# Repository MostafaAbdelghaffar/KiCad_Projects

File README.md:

# KiCad_Projects
Beginner friendly projects, to practice KiCad and design PCBs using KiCad

### Introduction: 
This Repo is made for beginner friendly KiCad design for training purposes. This acts as a portfolio for the trainings and projets I have worked for designing PCBs.

The first one "StopLight" is meant to be familiar with the KiCad tool as the training that I had was on Altium. It is a simple pcb design with 3 LEDs and 3 Resistors and a connector.

As a PCB designer you need to know the following:
1. Know the capabilities of your PCB manufacturer
2. Have a solid understanding of the PCB design process
3. Have a solid understanding of the PCB Design tools
4. Have the patience to build up your skills

### Description: 
#### The following are the GENERAL steps for designing PCB in order

1. Define design rules and requirement
2. Create a schematic: Detailed schematic of the board's electrical design
3. Place components (taking into account signal integrity, thermal management and manufacturability)
4. Route traces: use color coded route tracing to create cirtual pathways between components and determine ther most efficient design layout.
5. Add labels and identifiers: including markers and reference designator or other identifying information to the layout.
6. Insert drill holes

#### The following are the KiCad design workflow in order:
<div align="center">
  
  <p><em>Figure 1: KiCad Design Workflow<sup><a href="#footnote-1">1</a></sup></em></p>
</div>

### PCB design process:

<div align="center">
  
  <p><em>Figure 2: PCB Design Process<sup><a href="#footnote-2">2</b></sup></em></p>
</div>

### Results

<div align="center">
  
  <p><em>Figure 3: Schematic Capture</em></p>
</div>

<div align="center">
  
  <p><em>Figure 4: PCB Design</em></p>
</div>

<div align="center">
  
  <p><em>Figure 5: PCB 3D View</em></p>
</div>

### References:
* **Footnote 1**: Image source: [Tech Explorations](https://techexplorations.com/wp-content/uploads/2019/05/S1_KicadDesignProcess-1024x619.jpg)
* <b id="footnote-2"></a>**Footnote 2**: Image source: [TronicsZone](https://www.tronicszone.com/tronicszone/wp-content/uploads/2020/02/PCB-Manufacturing-Steps.png)

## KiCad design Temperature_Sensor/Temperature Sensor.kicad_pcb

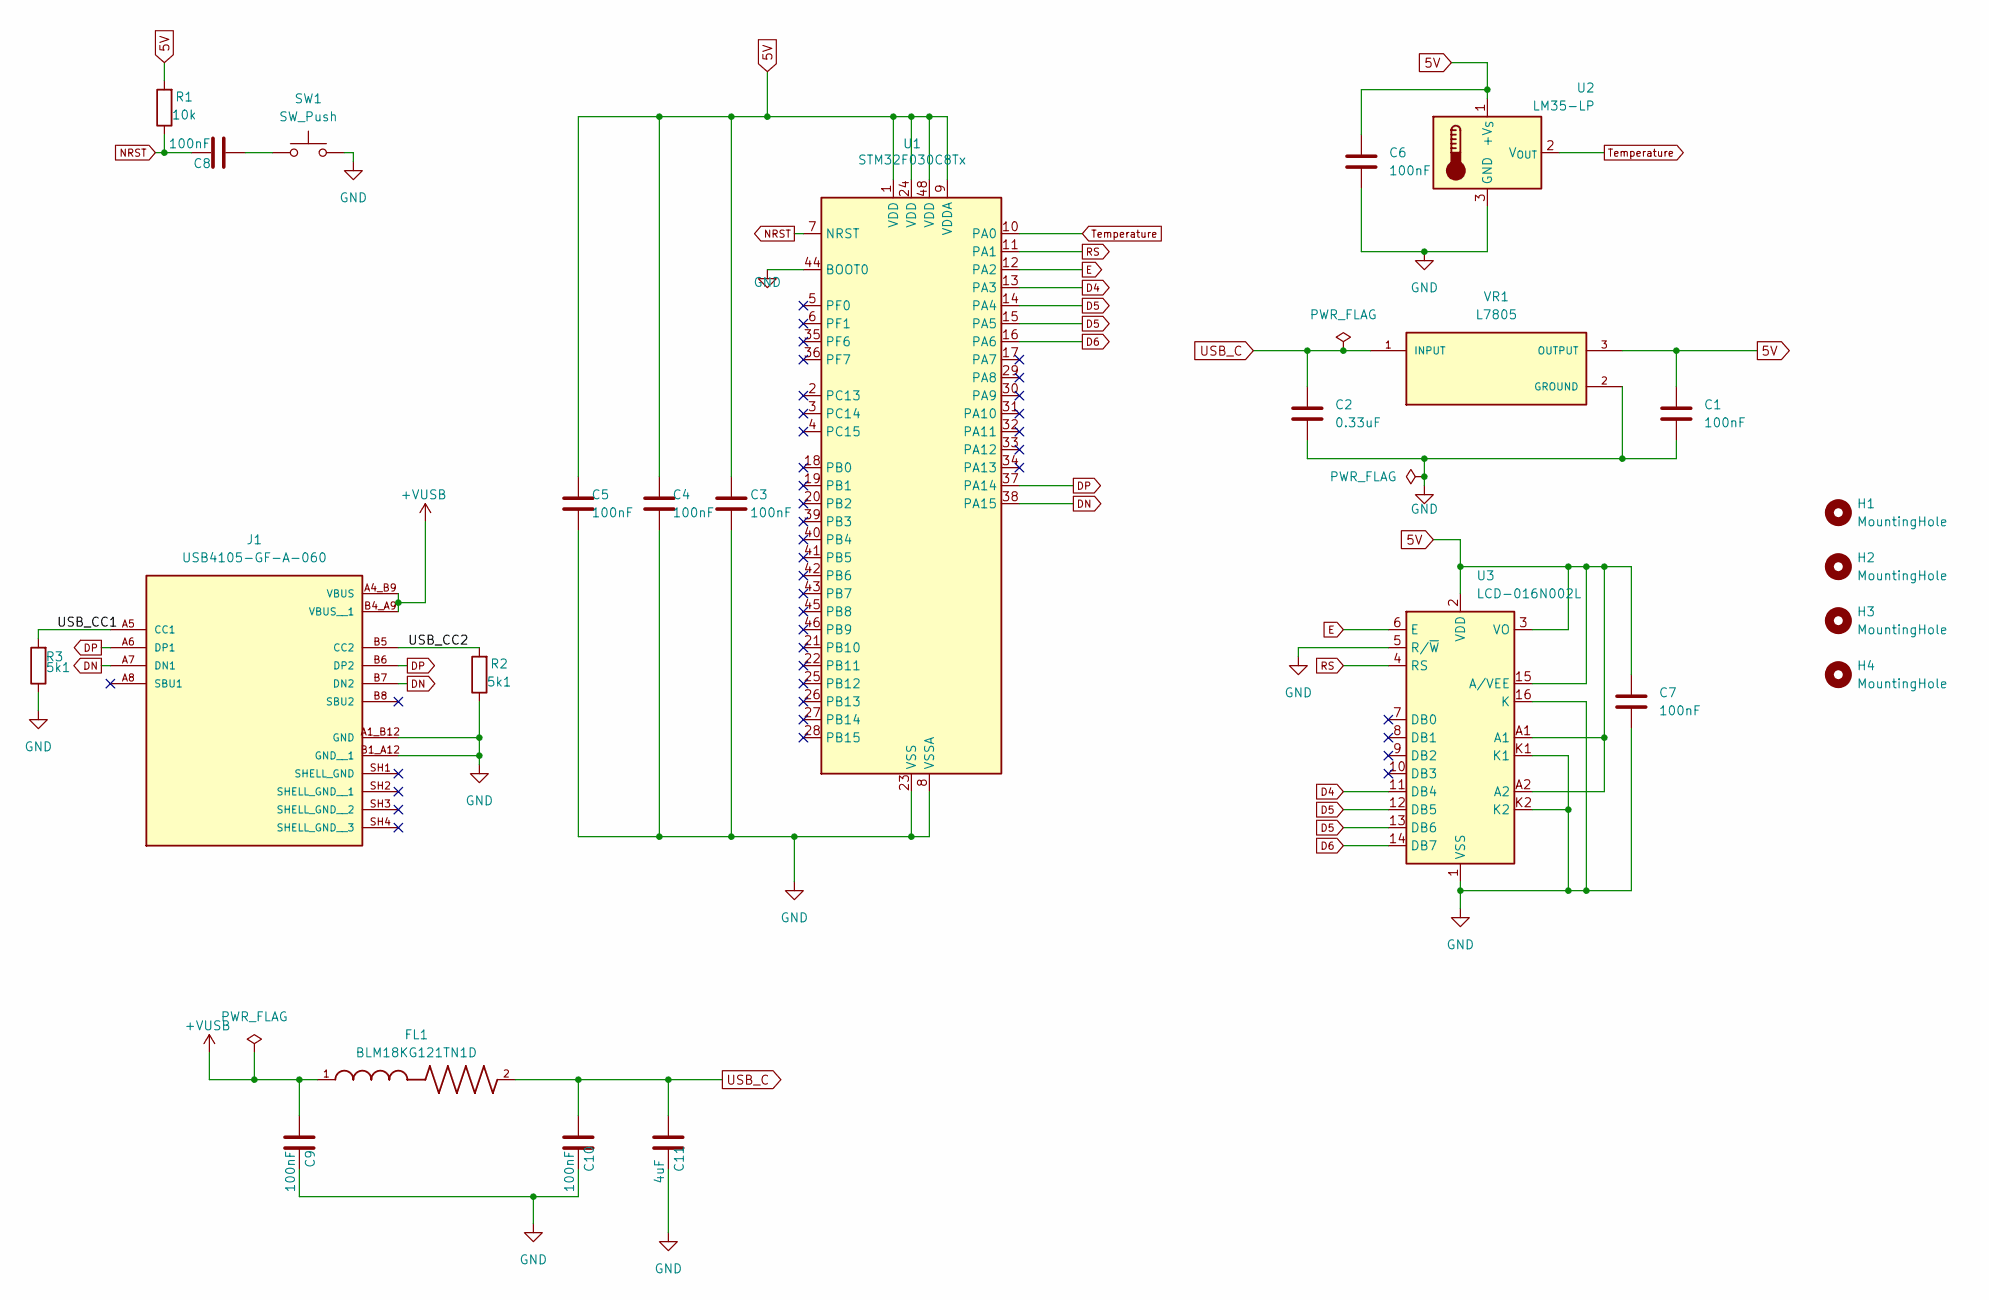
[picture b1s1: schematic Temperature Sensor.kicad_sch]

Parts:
C1, C3, C4, C5, C6, C7, C8, C9, C10: 100nF; C_0603_1608Metric
C2: 0.33uF; C_0603_1608Metric
C11: 4uF; C_0603_1608Metric
FL1: BLM18KG121TN1D; BEADC1608X75N
H1, H2, H3, H4: MountingHole; MountingHole_2.5mm
J1: USB4105-GF-A-060; GCT_USB4105-GF-A-060; PARTREV B3
R1: 10k; R_Axial_DIN0207_L6.3mm_D2.5mm_P7.62mm_Horizontal
R2, R3: 5k1; R_Axial_DIN0207_L6.3mm_D2.5mm_P7.62mm_Horizontal
SW1: SW_Push; SW_PUSH_6mm_H5mm
U1: STM32F030C8Tx; LQFP-48_7x7mm_P0.5mm
U2: LM35-LP; TO-92_Inline
U3: LCD-016N002L
VR1: L7805; TO255P1020X450X2000-3; PARTREV 36

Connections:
5V: C1.1, C3.1, C4.1, C5.1, C6.1, C7.1, R1.2, U1.1 (VDD), U1.9 (VDDA), U1.24 (VDD), U1.48 (VDD), U2.1 (+V_{S}), U3.2 (VDD), U3.3 (VO), U3.15 (A/VEE), U3.A1, U3.A2, VR1.3 (OUTPUT)
+VUSB: C9.2, FL1.1, J1.A4_B9 (VBUS), J1.B4_A9 (VBUS__1)
/USB_CC1: J1.A5 (CC1), R3.2
/USB_CC2: J1.B5 (CC2), R2.2
D4: U1.13 (PA3), U3.11 (DB4)
D5: U1.14 (PA4), U1.15 (PA5), U3.12 (DB5), U3.13 (DB6)
D6: U1.16 (PA6), U3.14 (DB7)
DN: J1.A7 (DN1), J1.B7 (DN2), U1.38 (PA15)
DP: J1.A6 (DP1), J1.B6 (DP2), U1.37 (PA14)
E: U1.12 (PA2), U3.6 (E)
GND: C1.2, C2.2, C3.2, C4.2, C5.2, C6.2, C7.2, C9.1, C10.1, C11.1, J1.A1_B12 (GND), J1.B1_A12 (GND__1), R2.1, R3.1, SW1.2, U1.8 (VSSA), U1.23 (VSS), U1.44 (BOOT0), U1.47 (VSS), U2.3 (GND), U3.1 (VSS), U3.5 (R/~W), U3.16 (K), U3.K1, U3.K2, VR1.2 (GROUND)
NRST: C8.1, R1.1, U1.7 (NRST)
unnamed: C8.2, SW1.1
RS: U1.11 (PA1), U3.4 (RS)
Temperature: U1.10 (PA0), U2.2 (V_{OUT})
USB_C: C2.1, C10.2, C11.2, FL1.2, VR1.1 (INPUT)

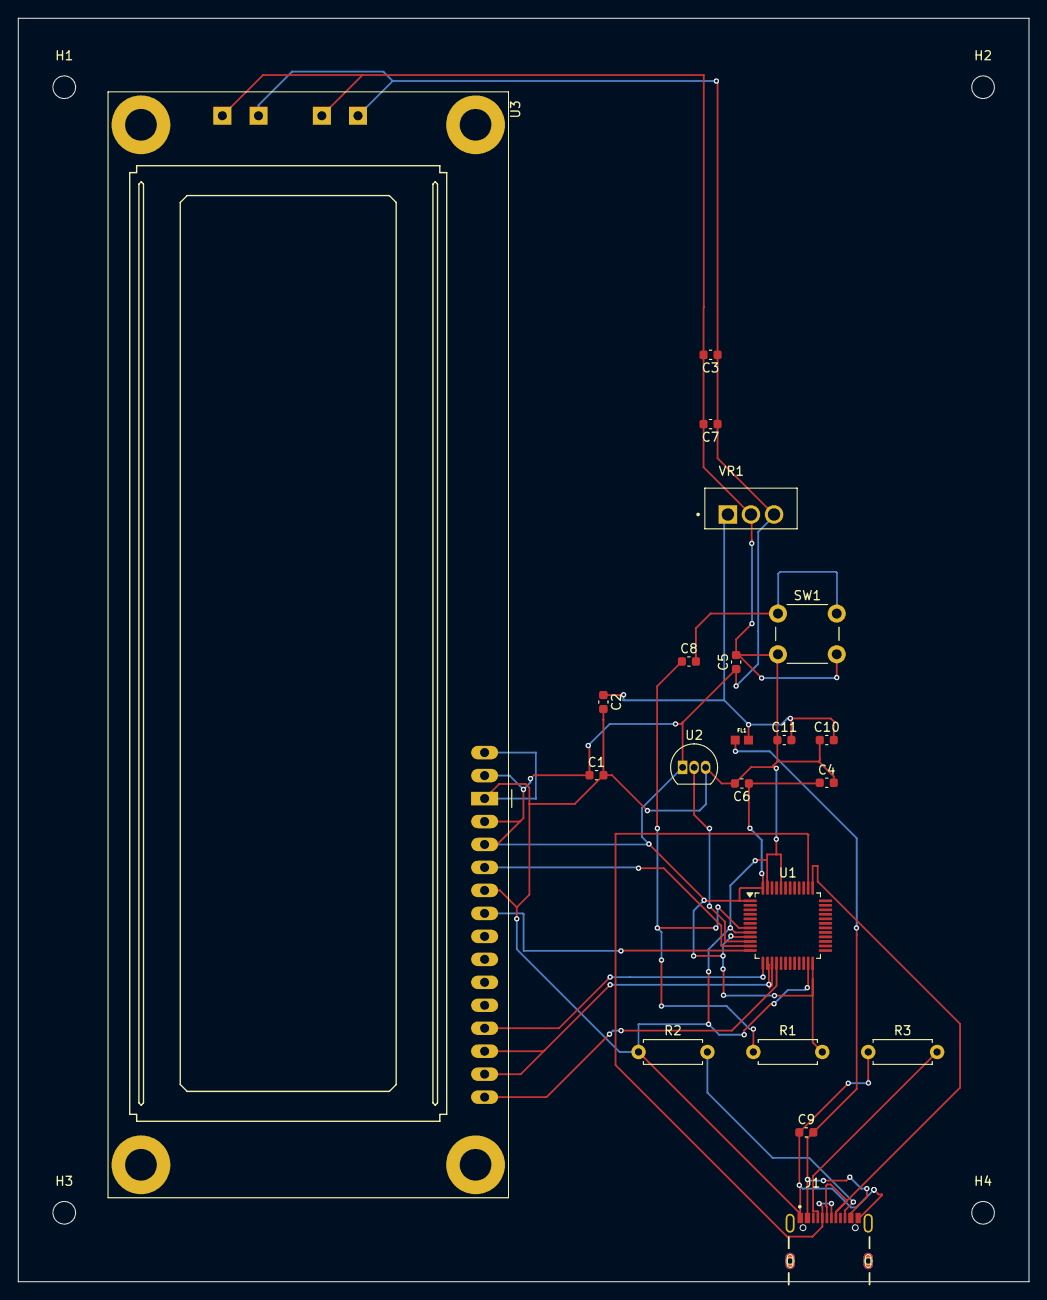
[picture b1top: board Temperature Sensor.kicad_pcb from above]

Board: 2 copper layers, 111.8 x 139.7 mm, 25 parts (0 on the bottom side), 16 nets.

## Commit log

2025-01-02 Update README.md
    Introduction
2025-01-02 Update README.md
    putting images in the middle
2025-01-02 Initial commit with existing files
2025-01-03 Adding git ignore
2025-01-03 ignore StopLight source files
2025-01-03 kosom el images
2025-01-03 Update README.md
    Updating the README.md with images in the result section
2025-01-09 adding project
2025-01-09 modified git ignore
2025-01-09 removced the files
2025-01-09 wnaby 3'or
